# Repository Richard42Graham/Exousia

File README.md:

# Exousia

project to make a USB-C compatable Buck Boost power suply, thats bi directonal for DRP (dual role power)

useing the ISL95338

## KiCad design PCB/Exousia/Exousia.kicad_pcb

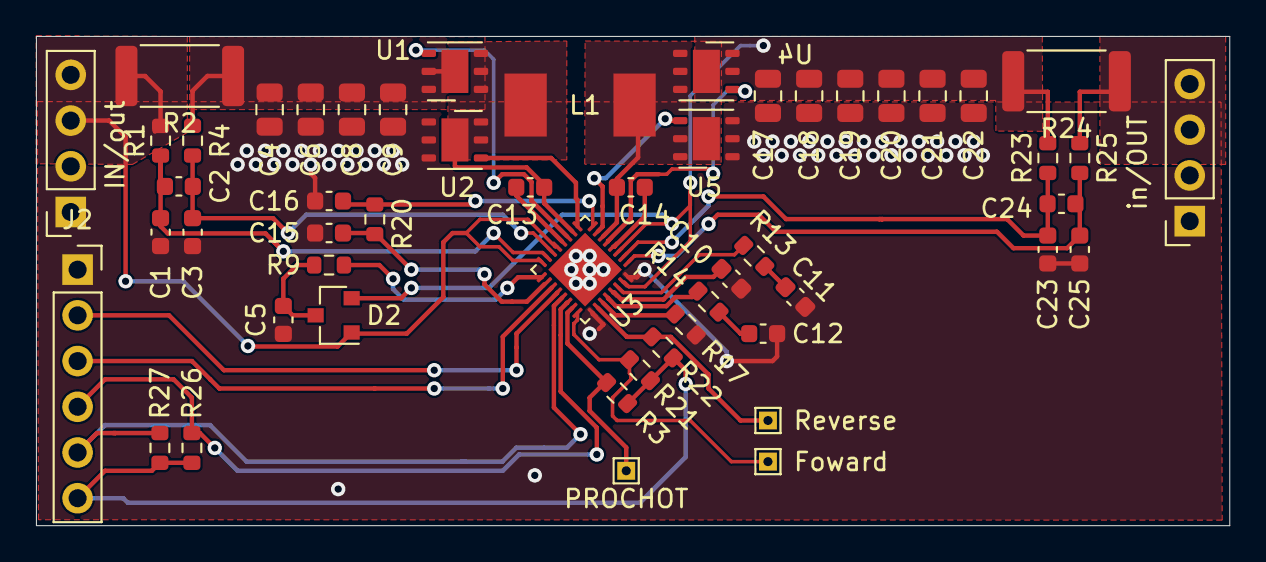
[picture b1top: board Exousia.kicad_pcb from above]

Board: 2 copper layers, 66.3 x 27.2 mm, 53 parts (0 on the bottom side), 35 nets.

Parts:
C1, C3, C5, C15, C16, C23, C25: 1uF; C_0603_1608Metric
C2, C24: 4.7uF; C_0603_1608Metric
C4, C6, C8, C9: 4.7uF; C_0805_2012Metric
C10: 1000pF; C_0603_1608Metric
C11, C12: 22nF; C_0603_1608Metric
C13, C14: 0.22uF; C_0603_1608Metric
C17, C18, C19, C20, C21, C22: 22uF; C_0805_2012Metric
D2: BAT54C; SOT-23
J1: IN/out; PinSocket_1x04_P2.54mm_Vertical
J2: Conn_01x06_Male; PinSocket_1x06_P2.54mm_Vertical
J3: in/OUT; PinSocket_1x04_P2.54mm_Vertical
L1: 0.82uH PIMB063T-R82MS-68; PIMB063T-R82MS-68
R1, R4, R9, R23, R25: 1R; R_0603_1608Metric
R2, R24: 0.005R; R_2512_6332Metric
R3, R21, R22: 3.3K; R_0603_1608Metric
R13, R14: 698; R_0603_1608Metric
R17: 133K; R_0603_1608Metric
R20: 4.7R; R_0603_1608Metric
R26, R27: 10K; R_0603_1608Metric
TP1: Foward; TestPoint_THTPad_1.0x1.0mm_Drill0.5mm
TP2: Reverse; TestPoint_THTPad_1.0x1.0mm_Drill0.5mm
TP3: PROCHOT; TestPoint_THTPad_1.0x1.0mm_Drill0.5mm
U1, U2, U4, U5: AON7410; DFN-6-1EP_3x3mm_P1mm_EP1.5x2.4mm
U3: ISL95338; QFN-32-1EP_4x4mm_P0.4mm_EP2.9x2.9mm

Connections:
+3V3: J2.6, R3.1, R21.1, R22.1, R26.1, R27.1
DCIN: R9.1, U3.17 (DCIN)
FRWPG: R21.2, TP1.1, U3.24 (FRWPG)
GND: C1.1, C3.1, C4.2, C5.2, C6.2, C8.2, C9.2, C10.2, C11.2, C12.2, C15.2, C16.2, C17.2, C18.2, C19.2, C20.2, C21.2, C22.2, C23.1, C25.1, J1.1, J1.2, J2.1, J3.1, J3.2, R17.2, U2.1 (S), U2.2 (S), U2.3 (S), U3.25 (ADDR0), U3.32 (ADDR1), U5.1 (S), U5.2 (S), U5.3 (S)
unnamed: C1.2, C2.2, R1.1, U3.15 (CSIP)
unnamed: C2.1, C3.2, R4.1, U3.14 (CSIN)
unnamed: C4.1, C6.1, C8.1, C9.1, R2.1, R4.2, U1.5 (D), U1.6 (D), U1.7 (D)
unnamed: C5.1, D2.3, R9.2
unnamed: C10.1, U3.29 (REF)
unnamed: C11.1, R13.2
unnamed: C12.1, R14.2
unnamed: C13.1, L1.1, U1.1 (S), U1.2 (S), U1.3 (S), U2.5 (D), U2.6 (D), U2.7 (D), U3.10 (PHASE1)
unnamed: C13.2, U3.12 (BOOT1)
unnamed: C14.1, L1.2, U3.6 (PHASE2), U4.1 (S), U4.2 (S), U4.3 (S), U5.5 (D), U5.6 (D), U5.7 (D)
unnamed: C14.2, U3.4 (BOOT2)
unnamed: C15.1, R20.2, U3.18 (VDD)
unnamed: C16.1, R20.1, U3.8 (VDDP)
unnamed: C17.1, C18.1, C19.1, C20.1, C21.1, C22.1, D2.2, R23.2, R24.2, U3.3 (VOUTS), U3.31 (VOUT), U4.5 (D), U4.6 (D), U4.7 (D)
unnamed: C23.2, C24.2, R23.1, U3.2 (CSOP)
unnamed: C24.1, C25.2, R25.1, U3.1 (CSON)
unnamed: D2.1, J1.3, J1.4, R1.2, R2.2, U3.13 (ADPS), U3.16 (ADP)
unnamed: J3.3, J3.4, R24.1, R25.2
unnamed: R13.1, U3.30 (COMPR)
unnamed: R14.1, U3.28 (COMPF)
unnamed: U1.4 (G), U3.11 (UGATE1)
unnamed: U2.4 (G), U3.9 (LGATE1)
unnamed: U3.5 (UGATE2), U4.4 (G)
unnamed: U3.7 (LGATE2), U5.4 (G)
unnamed: R17.1, U3.27 (PROG)
PROCHOT#: R3.2, TP3.1, U3.23 (PROCHOT#)
Pin_FRWEN: J2.3, U3.19 (FRWEN)
RVSEN: J2.2, U3.20 (RVSEN)
RVSPG: R22.2, TP2.1, U3.26 (RVSPG)
SCL: J2.4, R26.2, U3.22 (SCL)
SDA: J2.5, R27.2, U3.21 (SDA)

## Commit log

2020-11-27 inital commits?
2020-11-27 added main IC
2020-11-27 added more stuff
2020-11-27 added refrence design files
2020-11-29 added nice FETs and more detailed circuti diogram
2020-12-02 started adding footprints to all the components!
2020-12-02 done all but 1 footprints
2020-12-06 started layout of PCB, minus main inductor :C
2020-12-09 did a little bit of layout
2020-12-20 did work
2021-01-02 updated some footrpints and compoinent valeus for 12A
2021-01-02 did routing!
2021-01-07 finished most of the routing
2021-01-16 minor changes to the PCB
2021-04-14 minor pcb updates
2021-04-17 upgraded sens resitors to handle 12A max. and retrouted a bit
2023-05-23 improved the controle cirtitry for controleing the IC
